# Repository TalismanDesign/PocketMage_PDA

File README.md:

# PocketMage PDA

PocketMage is available on Crowd Supply! Check it out [there](https://pocketmage.org/back)!

@Ashtf 2025

<!-- markdownlint-disable MD033 -->

## [Project Summary]

  This project is a PDA powered by an ESP32-S3 running a custom OS written in C++ using PlatformIO. This project utilizes an E-Ink and OLED screen in tandem to mitigate the refresh rate restrictions of an E-Ink panel while retaining the aesthetics and benefits of using E-Ink. This project is a work in progress and currently amounts to a simple GUI for navigating between apps, a text (.txt) file editor, and a basic file manager. More applications are planned for the future and a list of TO-DOs can be found below.

  At this point, the plan for this project is to get the software and hardware to maturity and once a finished product is achieved, a few things will happen. First, the project files (Code, KiCad schematics, 3D files) will be open-sourced and free for anyone to access. Next, I will likely begin selling kits that allow people to purchase all the parts required to build a device for themselves if they don't want to source the parts themselves. Finally, the community will be encouraged to help develop the software for the device and hopefully push it even further than I could myself.

The project is open hardware and open software: the code, KiCad schematics, and 3D files are published under Apache-2.0. Kits are available on [Crowd Supply](https://pocketmage.org/back) for anyone who prefers not to source parts individually. Community contributions to the firmware and apps are welcome.

## [Getting Started]

Start with the docs sites. The PocketMageOS docs cover the device, the OS, and the built-in apps; the SDK docs cover building standalone apps.

- [PocketMageOS Docs](https://talismandesign.github.io/PocketMage_PDA/docs/)
- [Architecture](https://talismandesign.github.io/PocketMage_PDA/docs/development/architecture)
- [Build Environments](https://talismandesign.github.io/PocketMage_PDA/docs/development/build-environments)
- [Command Manual](https://talismandesign.github.io/PocketMage_PDA/docs/command-manual)
- [FAQ](https://talismandesign.github.io/PocketMage_PDA/docs/faq)
- [Scripting](https://talismandesign.github.io/PocketMage_PDA/docs/scripting)
- [PocketMage SDK Docs](https://talismandesign.github.io/PocketMage_SDK/docs/)

Apps come in two forms. **Native apps** compile into the firmware; start from [APP_TEMPLATE.cpp](./Code/PocketMageOS/src/APP_TEMPLATE.cpp) and the [App API Reference](https://talismandesign.github.io/PocketMage_PDA/docs/reference/app-api). **ELF apps** build standalone against the SDK and load from the SD card at runtime; start from the [SDK Get Started guide](https://talismandesign.github.io/PocketMage_SDK/docs/get-started/).

The app walkthrough video is a useful first pass: [Developing For the PocketMage](https://www.youtube.com/watch?v=3Ytc-3-BbMM).

## [Hardware]

- ESP32-S3 WROOM1 with 16 MB flash and 8 MB RAM. WiFi and Bluetooth supported.
- 3.1" 320x240px 1-bit SPI E-Ink panel (GDEQ031T10) with integrated driver
- 256x32px 1-bit SPI OLED (SSD1326, ER-OLED018-1W) with integrated driver
- MicroSD card slot with support for up to 2 TB
- TCA8418 I2C keyboard matrix IC
- Piezo buzzer (simple tones)
- Power button
- 1200 mAh pouch-style LiPo battery with JST PH (2 mm) connector
- USB Type-C connector
- PCF8563T I2C RTC module
- Expansion port with the following breakouts:
  - +3.3V
  - GND
  - I2C SDA
  - I2C SCL
  - SPI MOSI
  - SPI SCK
  - SPI MISO
  - GPIO A
  - GPIO B
  - GPIO C
  - GPIO D / UART TX (changeable with a solder jumper, default TX)
  - GPIO E / UART RX (changeable with a solder jumper, default RX)

## [Software]

- Text editor app (TXT)
- FileWiz file-management app
- Calendar app
- USB file transfer app
- COMM mesh chat app
- Settings app
- Tasks app
- Journal app
- Dictionary app (Lexicon)
- App loader for ELF apps
- Terminal app (Wrench scripting)
- SSH
- Commands supported through the home menu:
  - `roll dN` (dice roll, N = number of sides)
  - set time and date
  - directly open files in TXT or FileWiz by typing the name
  - and more

## [Planned Features]

- Timers and alarms
- E-book reader
- WiFi notes/calendar sync (Google Docs/Calendar)
- LoRa/Meshtastic add-on module
- Battery expansion add-on module
- Custom abbreviations
- Bluetooth keyboard support

## License

All files are distributed under the Apache-2.0 license:

PocketMage PDA - A clamshell note-taking and productivity device using E-Ink and OLED.

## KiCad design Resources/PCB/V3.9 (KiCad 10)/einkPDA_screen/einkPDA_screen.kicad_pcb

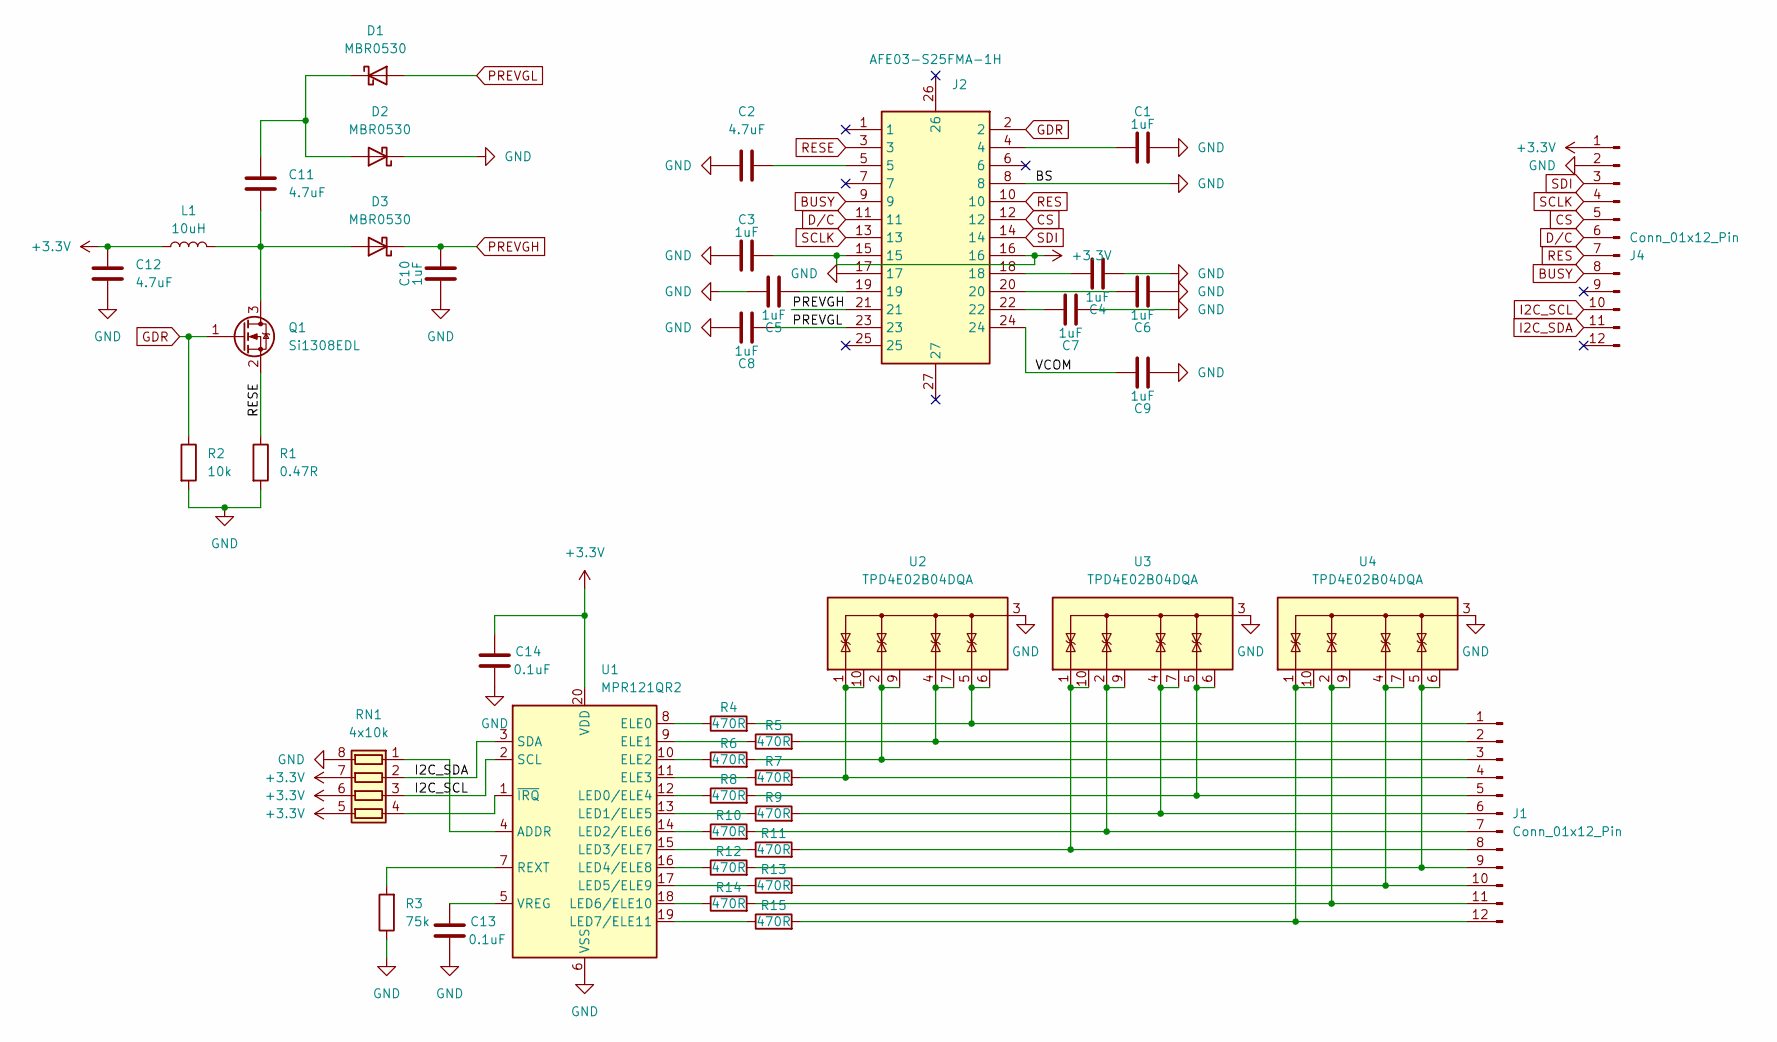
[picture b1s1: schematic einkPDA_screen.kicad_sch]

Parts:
C1, C3, C4, C5, C6, C7, C8, C9, C10: 1uF; C_0402_1005Metric; MPN C52923
C2, C11, C12: 4.7uF; C_0805_2012Metric; MPN C1779
C13, C14: 0.1uF; C_0402_1005Metric; MPN C1525
D1, D2, D3: MBR0530; D_SOD-123; MPN C77336
J1: Conn_01x12_Pin; TouchSlider-12_50x10mm
J2: AFE03-S25FMA-1H; MPN C262544
J4: Conn_01x12_Pin; AFC01-S12FCA-00; MPN C262661
L1: 10uH; L_Cenker_CKCS5020; MPN C52281
Q1: Si1308EDL; SOT-323_SC-70; MPN C7603347
R1: 0.47R; R_0603_1608Metric; MPN C3013349
R2: 10k; R_0805_2012Metric; MPN C17414
R3: 75k; R_0603_1608Metric; MPN C23242
R4, R5, R6, R7, R8, R9, R10, R11, R12, R13, R14, R15: 470R; R_0402_1005Metric; LCSC Part # C25117
RN1: 4x10k; R_Array_Concave_4x0603; MPN C29718
U1: MPR121QR2; UQFN-20_3x3mm_P0.4mm; MPN C91322
U2, U3, U4: TPD4E02B04DQA; USON-10_2.5x1.0mm_P0.5mm

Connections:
+3.3V: C3.2, C12.1, C14.1, J2.15, J2.16, J4.1, L1.1, RN1.5 (R4.2), RN1.6 (R3.2), RN1.7 (R2.2), U1.20 (VDD)
/VCOM: C9.2, J2.24
BUSY: J2.9, J4.8
CS: J2.12, J4.5
D/C: J2.11, J4.6
GDR: J2.2, Q1.1 (G), R2.1
GND: C1.2, C2.1, C3.1, C4.1, C5.2, C6.1, C7.1, C8.2, C9.1, C10.1, C12.2, C13.2, C14.2, D2.1 (K), J2.8, J2.17, J4.2, R1.2, R2.2, R3.1, RN1.8 (R1.2), U1.6 (VSS), U2.3 (G), U2.8 (G), U3.3 (G), U3.8 (G), U4.3 (G), U4.8 (G)
I2C_SCL: J4.10, RN1.3 (R3.1), U1.2 (SCL)
I2C_SDA: J4.11, RN1.2 (R2.1), U1.3 (SDA)
unnamed: C1.1, J2.4
unnamed: C2.2, J2.5
unnamed: C4.2, J2.18
unnamed: C5.1, J2.19
unnamed: C6.2, J2.20
unnamed: C7.2, J2.22
unnamed: C11.1, D1.1 (K), D2.2 (A)
unnamed: C11.2, D3.2 (A), L1.2, Q1.3 (D)
unnamed: J1.1, R4.2, U2.5 (IO4), U2.6 (NC)
unnamed: J1.2, R5.2, U2.4 (IO3), U2.7 (NC)
unnamed: J1.3, R6.2, U2.2 (IO2), U2.9 (NC)
unnamed: J1.4, R7.2, U2.1 (IO1), U2.10 (NC)
unnamed: J1.5, R8.2, U3.5 (IO4), U3.6 (NC)
unnamed: J1.6, R9.2, U3.4 (IO3), U3.7 (NC)
unnamed: J1.7, R10.2, U3.2 (IO2), U3.9 (NC)
unnamed: J1.8, R11.2, U3.1 (IO1), U3.10 (NC)
unnamed: J1.9, R12.2, U4.5 (IO4), U4.6 (NC)
unnamed: J1.10, R13.2, U4.4 (IO3), U4.7 (NC)
unnamed: J1.11, R14.2, U4.2 (IO2), U4.9 (NC)
unnamed: J1.12, R15.2, U4.1 (IO1), U4.10 (NC)
unnamed: RN1.1 (R1.1), U1.4 (ADDR)
unnamed: RN1.4 (R4.1), U1.1 (~IRQ)
unnamed: R4.1, U1.8 (ELE0)
unnamed: R5.1, U1.9 (ELE1)
unnamed: R6.1, U1.10 (ELE2)
unnamed: R7.1, U1.11 (ELE3)
unnamed: R8.1, U1.12 (LED0/ELE4)
unnamed: R9.1, U1.13 (LED1/ELE5)
unnamed: R10.1, U1.14 (LED2/ELE6)
unnamed: R11.1, U1.15 (LED3/ELE7)
unnamed: R12.1, U1.16 (LED4/ELE8)
unnamed: R13.1, U1.17 (LED5/ELE9)
unnamed: R14.1, U1.18 (LED6/ELE10)
unnamed: R15.1, U1.19 (LED7/ELE11)
unnamed: R3.2, U1.7 (REXT)
unnamed: C13.1, U1.5 (VREG)
PREVGH: C10.2, D3.1 (K), J2.21
PREVGL: C8.1, D1.2 (A), J2.23
RES: J2.10, J4.7
RESE: J2.3, Q1.2 (S), R1.1
SCLK: J2.13, J4.4
SDI: J2.14, J4.3

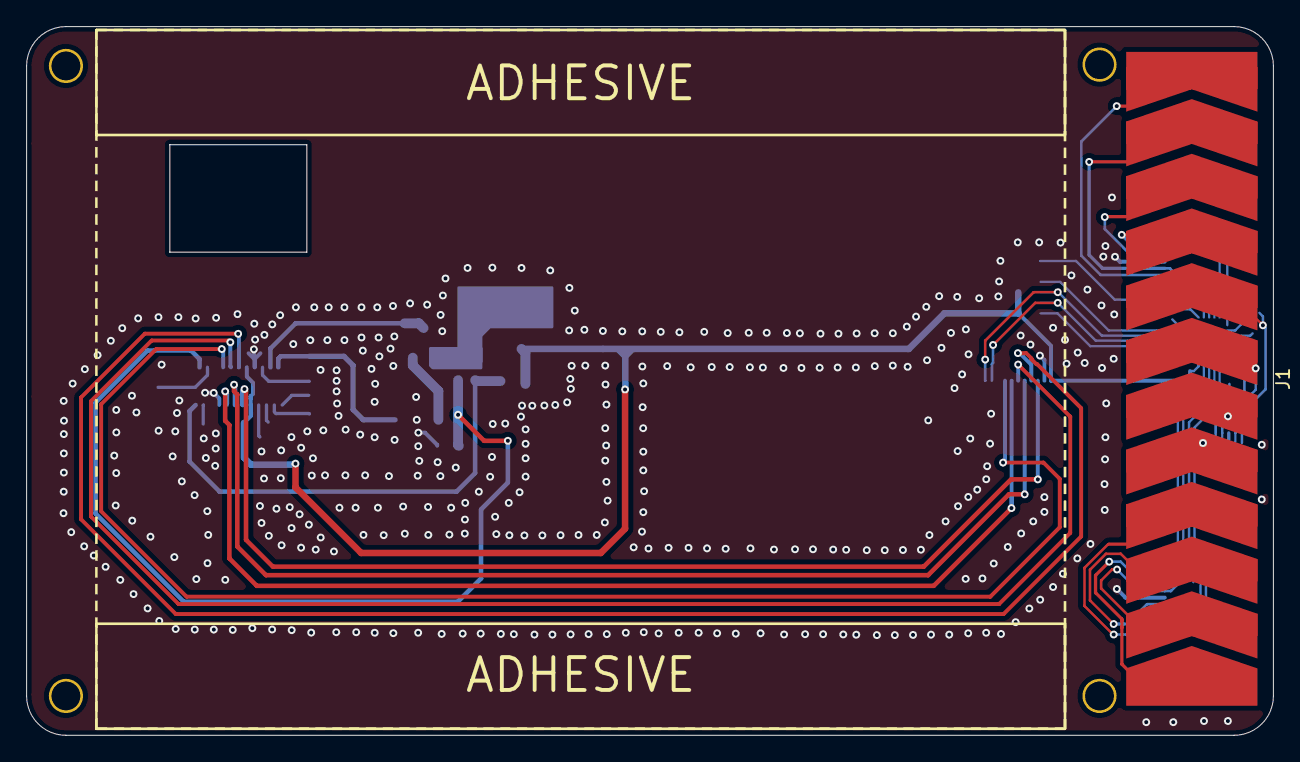
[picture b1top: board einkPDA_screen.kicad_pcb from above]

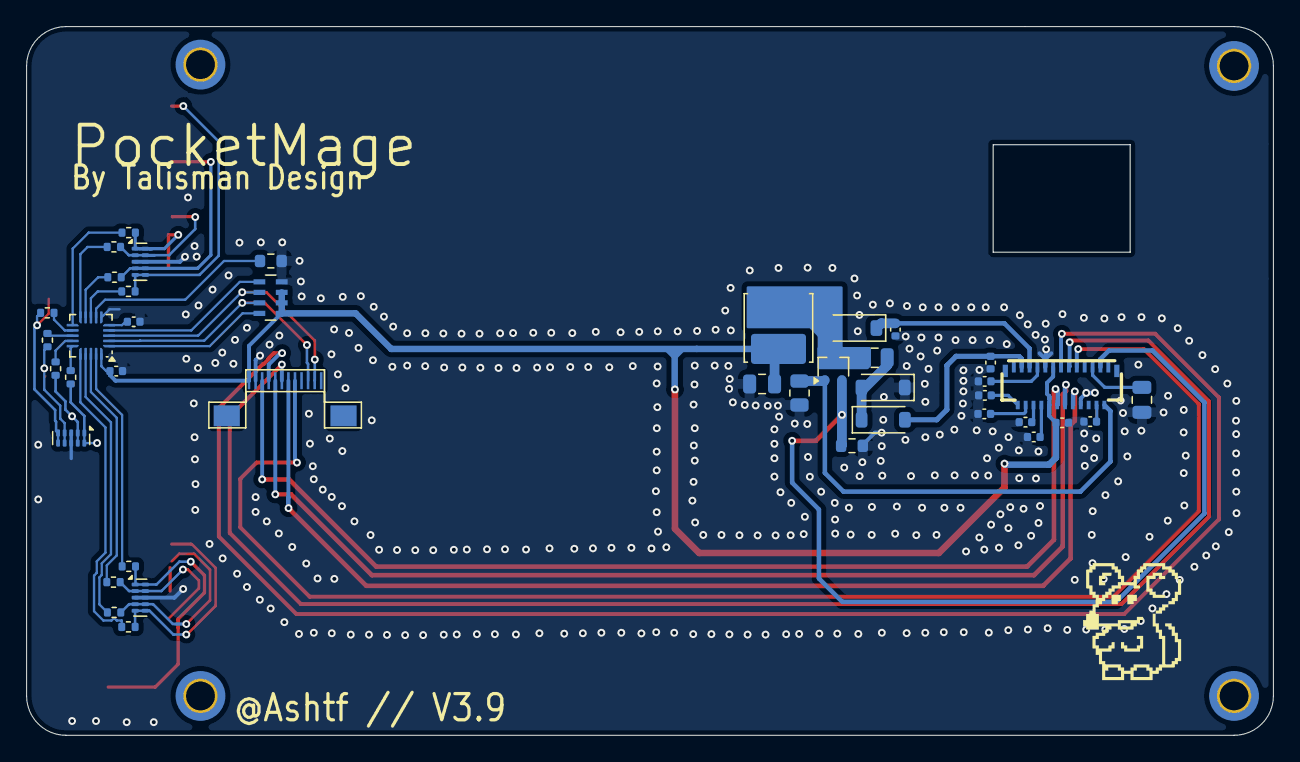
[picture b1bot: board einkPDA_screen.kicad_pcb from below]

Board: 2 copper layers, 95.0 x 54.0 mm, 42 parts (41 on the bottom side), 51 nets.

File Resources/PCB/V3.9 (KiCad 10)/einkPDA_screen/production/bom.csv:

Designator,Footprint,Quantity,Value,LCSC Part #
"C1, C10, C3, C4, C5, C6, C7, C8, C9",0402,9,1uF,C52923
"C11, C12, C2",0805,3,4.7uF,C1779
"C13, C14",0402,2,0.1uF,C1525
"D1, D2, D3",D_SOD-123,3,MBR0530,C77336
J1,TouchSlider-12_50x10mm,1,Conn_01x12_Pin,
J2,AFE03-S25FMA-1H,1,~,C262544
J4,AFC01-S12FCA-00,1,Conn_01x12_Pin,C262661
L1,L_Cenker_CKCS5020,1,10uH,C52281
Q1,SOT-323_SC-70,1,Si1308EDL,C7603347
R1,0603,1,0.47R,C3013349
"R10, R11, R12, R13, R14, R15, R4, R5, R6, R7, R8, R9",0402,12,470R,C25117
R2,0805,1,10k,C17414
R3,0603,1,75k,C23242
RN1,R_Array_Concave_4x0603,1,4x10k,C29718
U1,UQFN-20_3x3mm_P0.4mm,1,MPR121QR2,C91322
"U2, U3, U4",USON-10_2.5x1.0mm_P0.5mm,3,TPD4E02B04DQA,

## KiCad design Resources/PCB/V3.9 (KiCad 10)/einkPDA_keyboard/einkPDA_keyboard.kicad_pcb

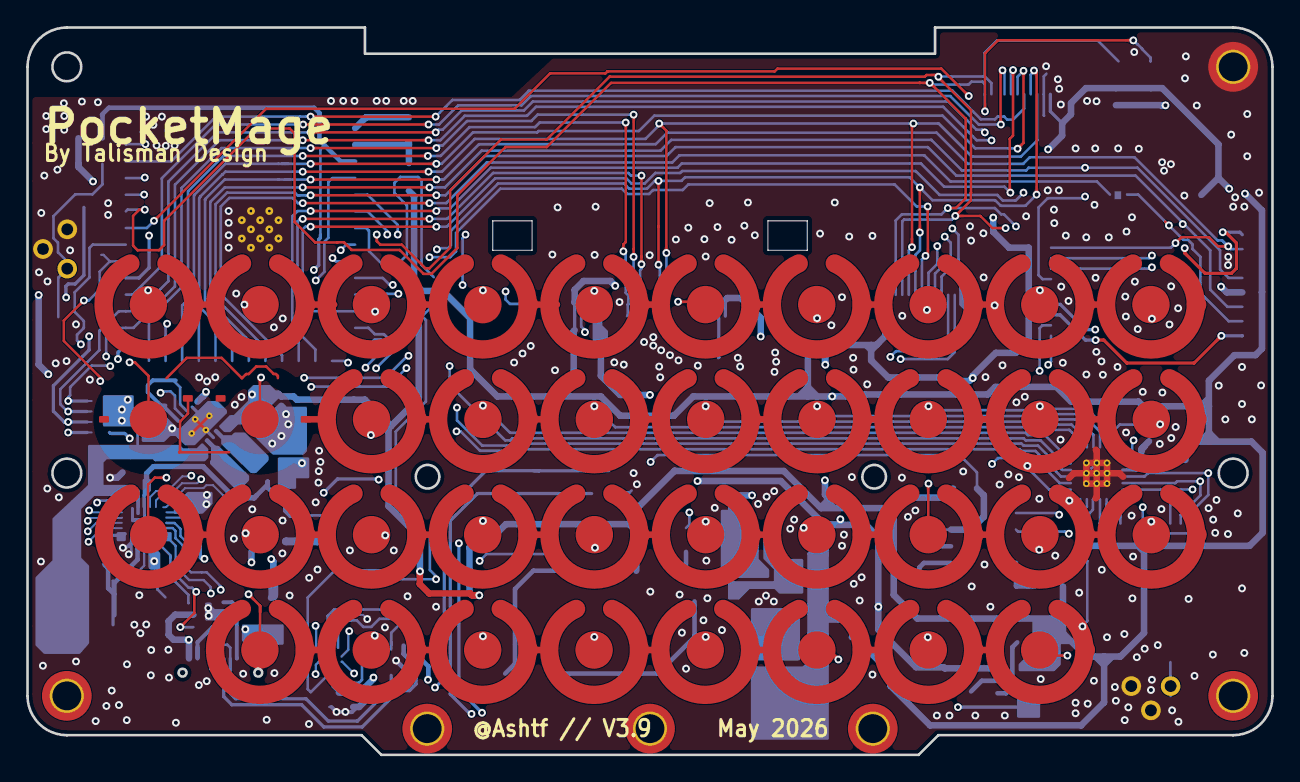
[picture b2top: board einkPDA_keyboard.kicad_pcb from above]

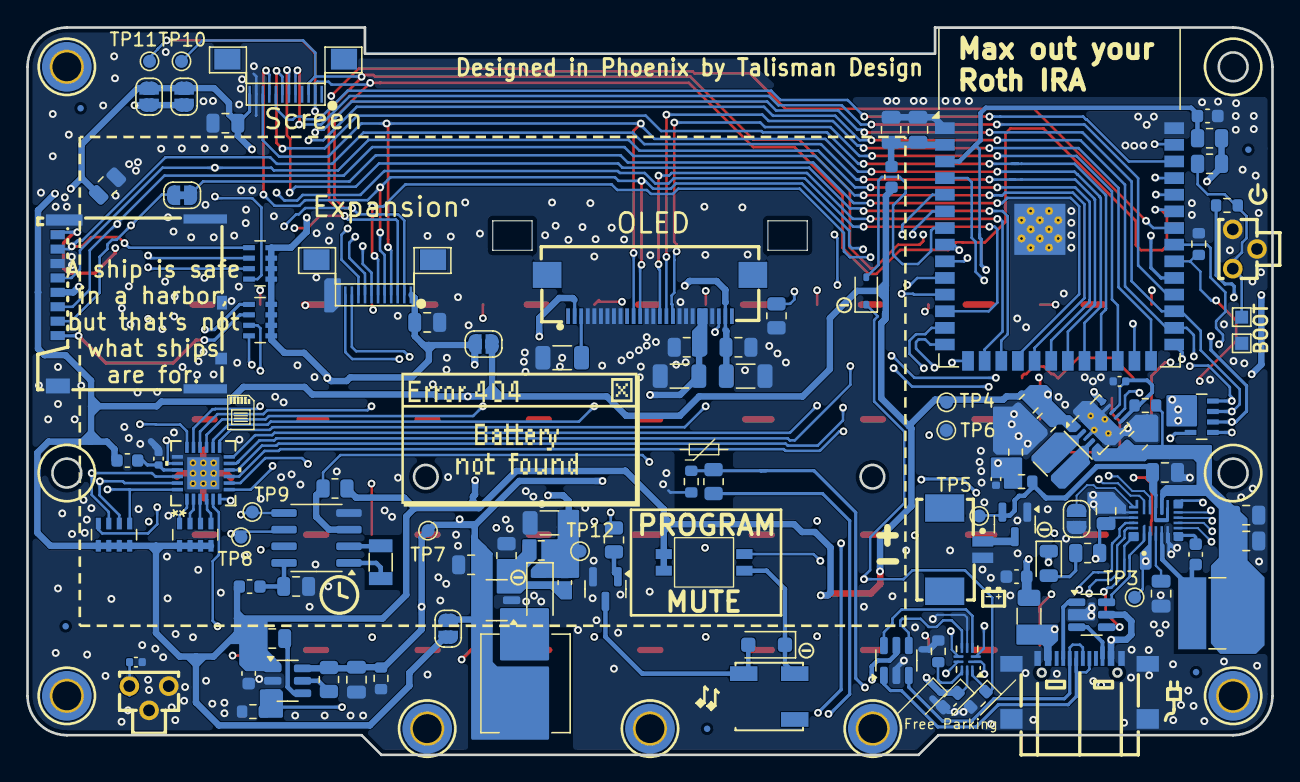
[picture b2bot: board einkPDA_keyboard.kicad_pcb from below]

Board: 4 copper layers, 95.0 x 55.5 mm, 148 parts (110 on the bottom side), 106 nets.

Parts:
BZ1: Buzzer; BUZ-SMD_3P_L5.0-W5.0-P3.50-TL
C1, C4, C6, C20: 1uF; C_0603_1608Metric
C2, C9: 100nF; C_0805_2012Metric
C3, C21, C22: 22uF; C_0805_2012Metric
C5: 47uF; C_0805_2012Metric
C7, C8, C19, C33: 0.1uF; C_0402_1005Metric
C10, C23, C24, C26, C28, C29, C30, C31, C32: 10uF; C_0805_2012Metric
C11: 4.7pF; C_0603_1608Metric
C12, C13, C14, C16: 4.7uF; C_1206_3216Metric
C15, C17: .1uF; C_0805_2012Metric
C18: 680pF; C_0805_2012Metric
C25: 4.7uF; C_0805_2012Metric
C27: 22nF; C_0603_1608Metric
D1: KT-0805Y; LED_0805_2012Metric
D2: MBR0530; D_SOD-123
D3: SM4007; D_SOD-123F
D5: D_Schottky; D_SOD-323
F1: 3A FUSE; Fuse_1206_3216Metric
FB1, FB2, FB3: FerriteBead; L_0603_1608Metric
J1: USB_C_Receptacle_USB2.0_16P; USB-TYPE-C-SMD_TYPE-C-16P-QTWT
J2, J5: Conn_01x12_Pin; AFC01-S12FCA-00
J3: Conn_01x26_Pin; FPC-SMD_AFC24-S26FIA [DUAL-SIDE]
J4: Micro_SD_Card; TF-SMD_503398-1892
J6: C2764211; CONN-SMD_532610271
JP1: SolderJumper_2_Bridged; SolderJumper-2_P1.3mm_Bridged_RoundedPad1.0x1.5mm
JP2, JP6, JP7, JP8, JP9: SolderJumper_2_Open; SolderJumper-2_P1.3mm_Open_RoundedPad1.0x1.5mm
L1: 10uH; L_Chilisin_BMRx00060630
L2: 1uH; L_Ferrocore_DLG-0504
L3: 2.2uH; L_Wurth_WE-LQSH-3012
Q1: MMBT3904; SOT-23
Q2: AO3401A; SOT-23
R1, R14: 10K; R_0805_2012Metric
R2, R8: 100R; R_0603_1608Metric
R3: 4.7k; R_0603_1608Metric
R4: 1k; R_0603_1608Metric
R5, R15: 470R; R_0805_2012Metric
R6, R7, R9, R19: 100K; R_0603_1608Metric
R11, R16: 2k; R_0805_2012Metric
R12: 1.8M; R_0805_2012Metric
R13: 205k; R_0805_2012Metric
R17: 10k; R_0805_2012Metric
R18: 10k; R_0603_1608Metric
R20: 680k; R_0805_2012Metric
RN1, RN2, RN3, RN4, RN5: 4x10k; R_Array_Concave_4x0603
SW1, SW3, SW5, SW6, SW7, SW9, SW10, SW11, SW12, SW13, SW14, SW15, SW16, SW17, SW18, SW19, SW20, SW21, SW22, SW23, SW24, SW25, SW26, SW27, SW28, SW29, SW30, SW31, SW32, SW33, SW34, SW35, SW37, SW38, SW39, SW40: contact_pad_SINGLE
SW2: contactPad_cutoutR
SW4: SW_DIP_x02; 2X_DIP_DHN-02-V-TR
SW8: contactPad_cutoutL
SW36, SW41: YTS-C017-2B; KEY-TH_3P-L4.5-W4.5-P3.0-EH
TH1: NTC; R_0603_1608Metric
TP1, TP2: TestPoint; TestPoint_Pad_1.0x1.0mm
TP3, TP4, TP5, TP6, TP7, TP8, TP9, TP10, TP11, TP12: TestPoint; TestPoint_Pad_D1.0mm
U1: ESP32-S3-WROOM-1-N16R2; ESP32-S3-WROOM-1
U2, U6: USBLC6-2SC6; SOT-23-6
U3: TPS63001; Texas_DRC0010J_ThermalVias
U4: PCF8563T; SOIC-8_3.9x4.9mm_P1.27mm
U5: TCA8418RTWR; RTW24_2P45X2P45
U7: TPS61040DBV; SOT-23-5
U8: TPS22917DBV; SOT-23-6
U9: MP2722GRH-0000-Z; IC_MP2722GRH-0000-Z
U10: TS3USB30ERSWR; UQFN-10_1.4x1.8mm_P0.4mm
Y1: Crystal_32.768kHz; Crystal_SMD_3215-2Pin_3.2x1.5mm

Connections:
+3.3V: C4.2, C6.2, C18.1, C31.2, C32.2, FB1.1, FB2.2, FB3.1, JP2.2 (B), JP7.2 (B), JP8.2 (B), JP9.2 (B), R1.1, R11.2, R14.1, RN1.1 (R1.1), RN1.2 (R2.1), RN1.3 (R3.1), RN1.4 (R4.1), RN2.5 (R4.2), RN2.6 (R3.2), RN2.7 (R2.2), RN2.8 (R1.2), RN4.5 (R4.2), RN4.6 (R3.2), RN4.7 (R2.2), SW4.1, SW4.2, TP4.1 (1_1), U3.1 (VOUT), U3.10 (FB), U8.1 (VIN), U10.9 (VCC)
+12V: C11.2, C12.1, C13.1, C15.1, D2.1 (K), J3.2, J3.25, R12.1, TP12.1 (1_1)
BAT+: C26.2, Q2.2 (S), R6.1, TP5.1 (1_1), U9.12 (BATTSNS), U9.14 (BATT)
BAT_MEAS: C19.1, R6.2, R7.1, U1.4 (IO4)
BMS_INT: RN4.4 (R4.1), U1.33 (IO40), U9.8 (~INT)
BOOT: R8.1, R14.2, SW36.1, TP1.1 (1_1)
BUZZER: R15.1, U1.10 (IO17)
BZ_CUTOFF: BZ1.1 (+), D3.1 (K), SW4.3
E-PAPER_BUSY: J2.5, U1.30 (IO37)
E-PAPER_CS: J2.8, U1.38 (IO2)
E-PAPER_D/C: J2.7, U1.23 (IO21)
E-PAPER_RES: J2.6, U1.17 (IO9)
EN: C1.2, C33.1, R1.2, SW41.1, U1.3 (EN)
ESP_D+: U1.14 (IO20), U10.2 (D2+)
ESP_D-: U1.13 (IO19), U10.6 (D2-)
EX_A: J5.7, U1.15 (IO3)
EX_B: J5.8, U1.11 (IO18)
EX_C: J5.9, U1.34 (IO41)
GND: C1.1, C2.1, C3.1, C4.1, C5.2, C6.1, C7.2, C8.2, C9.1, C10.1, C12.2, C13.2, C14.2, C15.2, C16.2, C17.2, C19.2, C20.1, C21.1, C22.1, C23.1, C24.2, C25.2, C26.1, C28.1, C29.1, C30.1, C31.1, C32.1, C33.2, J1.A1 (GND), J1.A12 (GND), J1.S1 (SHIELD), J2.11, J3.4, J3.5, J3.6, J3.7, J3.8, J3.9, J3.13, J3.14, J3.18, J3.19, J3.20, J3.23, J4.6 (VSS), J4.9 (SHIELD), J5.12, J6.3 (BATT-), JP6.1 (A), Q1.2 (E), Q2.1 (G), R3.2, R4.2, R7.2, R9.2, R13.2, R18.2, R19.2, R20.2, SW36.2, SW36.3 (GND), SW41.2, SW41.3 (GND), TH1.2, TP2.1 (1_1), TP6.1 (1_1), U1.1 (GND), U1.40 (GND), U1.41 (GND), U2.2 (GND), U3.3 (PGND), U3.9 (GND), U3.11 (PGND), U4.4 (VSS), U5.19 (GND), U5.25 (EPAD), U6.2 (GND), U7.2 (GND), U8.2 (GND), U9.5 (PGND), U9.18 (AGND), U10.4 (GND)
I2C_SCL: RN1.6 (R3.2), RN4.2 (R2.1), TP8.1 (1_1), U1.28 (IO35), U4.6 (SCL), U5.23 (SCL), U9.16 (SCL)
I2C_SCL_SWITCHED: J2.3, J5.3, RN5.7 (R2.2), TP10.1 (1_1), U1.25 (IO48)
I2C_SDA: RN1.7 (R2.2), RN4.3 (R3.1), TP9.1 (1_1), U1.29 (IO36), U4.5 (SDA), U5.22 (SDA), U9.15 (SDA)
I2C_SDA_SWITCHED: J2.2, J5.2, RN5.8 (R1.2), TP11.1 (1_1), U1.35 (IO42)
IC_D+: U9.21 (D+), U10.1 (D1+)
IC_D-: U9.20 (D-), U10.7 (D1-)
KB_INT: RN1.5 (R4.2), U1.12 (IO8), U5.24 (*INT)
LOAD: R19.1, U1.31 (IO38), U8.3 (ON)
unnamed: BZ1.2 (-), D3.2 (A), Q1.3 (C)
unnamed: D1.2 (A), R16.1
unnamed: D1.1 (K), U9.11 (STAT/IB)
unnamed: D2.2 (A), L1.2, U7.1 (SW)
unnamed: D5.1 (K), R18.1, SW4.4, U10.10 (S)
unnamed: J1.A5 (CC1), U6.1 (I/O1)
unnamed: J1.B5 (CC2), U6.3 (I/O2)
unnamed: J1.A6 (D+), J1.B6 (D+), U2.1 (I/O1)
unnamed: J1.A7 (D-), J1.B7 (D-), U2.3 (I/O2)
unnamed: C14.1, J3.3
unnamed: J3.24, R20.1
unnamed: J4.2 (DAT3/CD), JP1.2 (B), RN3.7 (R2.2)
unnamed: J6.1 (BATT+), Q2.3 (D)
unnamed: JP6.2 (B), U9.17 (~RST)
unnamed: Q1.1 (B), R15.2
unnamed: RN1.8 (R1.2), U5.20 (*RESET)
unnamed: RN2.1 (R1.1), U5.4 (ROW4)
unnamed: RN2.2 (R2.1), U5.3 (ROW5)
unnamed: RN2.3 (R3.1), U5.2 (ROW6)
unnamed: RN2.4 (R4.1), U5.1 (ROW7)
unnamed: RN4.1 (R1.1), U9.9 (PG/NTC2)
unnamed: C25.1, R16.2, RN4.8 (R1.2), U9.19 (VCC)
unnamed: C2.2, C3.2, FB1.2, U1.2 (3V3)
unnamed: R8.2, U1.27 (IO0)
unnamed: F1.1, J1.A4 (VBUS), J1.A9 (VBUS), U2.5 (VBUS), U6.5 (VBUS)
unnamed: C7.1, R2.1, U3.6 (EN), U3.8 (VINA)
unnamed: L3.1, U3.4 (L1)
unnamed: L3.2, U3.2 (L2)
unnamed: U4.1 (OSCI), Y1.1
unnamed: U4.2 (OSCO), Y1.2
unnamed: C9.2, FB3.2, U4.8 (VDD)
unnamed: C8.1, FB2.1, U5.21 (VCC)
unnamed: C11.1, R12.2, R13.1, U7.3 (FB)
unnamed: C18.2, U8.4 (CT)
unnamed: R5.2, U8.5 (QOD)
unnamed: C27.2, U9.6 (BST)
unnamed: U6.6 (I/O1), U9.1 (CC1)
unnamed: U6.4 (I/O2), U9.22 (CC2)
unnamed: R17.1, TH1.1, U9.10 (NTC1)
unnamed: C23.2, U9.3 (PMID)
unnamed: C27.1, L2.1, U9.4 (SW)
unnamed: R17.2, U9.7 (VRNTC)
unnamed: R3.1, U10.8 (~OE)
OLED_CS: J3.17, U1.24 (IO47)
OLED_D/C: J3.15, U1.16 (IO46)
OLED_RES: J3.16, U1.26 (IO45)
PWR_SAVE: R9.1, U1.32 (IO39), U3.7 (PS/SYNC)
RTC_INT: R11.1, U1.39 (IO1), U4.3 (~INT)
RX: J5.11, U1.36 (RXD0)
SD_CLK: J4.5 (CLK), RN3.8 (R1.2), U1.20 (IO12)
SD_CMD: J4.3 (CMD), RN3.6 (R3.2), U1.19 (IO11)
SD_CS: JP1.1 (A), U1.18 (IO10)
SD_D0: J4.7 (DAT0), RN3.5 (R4.2), U1.21 (IO13)
SD_D1: J4.8 (DAT1), RN5.5 (R4.2), U1.5 (IO5)
SD_D2: J4.1 (DAT2), RN5.6 (R3.2), U1.6 (IO6)
SPI_MISO_SWITCHED: J5.6, U1.9 (IO16)
SPI_MOSI_SWITCHED: J2.10, J3.11, J5.4, U1.22 (IO14)
SPI_SCK_SWITCHED: J2.9, J3.12, J5.5, U1.8 (IO15)
TX: J5.10, U1.37 (TXD0)
USB_5V: C20.2, F1.2, TP3.1 (1_1), U9.2 (IN)
USB_D+: U2.6 (I/O1), U10.3 (D+)
USB_D-: U2.4 (I/O2), U10.5 (D-)
USB_SW: D5.2 (A), U1.7 (IO7)
V_LOADSWITCH: C5.1, C10.2, C16.1, C17.1, C21.2, C22.2, C24.1, J2.12, J3.21, J3.22, J4.4 (VDD), J5.1, JP2.1 (A), JP7.1 (A), JP8.1 (A), JP9.1 (A), L1.1, R4.1, R5.1, RN3.1 (R1.1), RN3.2 (R2.1), RN3.3 (R3.1), RN3.4 (R4.1), RN5.1 (R1.1), RN5.2 (R2.1), RN5.3 (R3.1), RN5.4 (R4.1), TP7.1 (1_1), U7.4 (EN), U7.5 (VIN), U8.6 (VOUT)
V_SYS: C28.2, C29.2, C30.2, L2.2, R2.2, U3.5 (VIN), U9.13 (SYS)
col1: SW1.1, SW2.1, SW3.1, U5.9 (COL0)
col2: SW7.1, SW8.1, SW9.1, SW10.1, U5.10 (COL1)
col3: SW13.1, SW14.1, SW15.1, SW16.1, U5.11 (COL2)
col4: SW19.1, SW20.1, SW21.1, SW22.1, U5.12 (COL3)
col5: SW25.1, SW26.1, SW27.1, SW28.1, U5.13 (COL4)
col6: SW31.1, SW32.1, SW33.1, SW34.1, U5.14 (COL5)
col7: SW37.1, SW38.1, SW39.1, SW40.1, U5.15 (COL6)
col8: SW5.1, SW6.1, SW11.1, SW12.1, U5.16 (COL7)
col9: SW17.1, SW18.1, SW23.1, SW24.1, U5.17 (COL8)
col10: SW29.1, SW30.1, SW35.1, U5.18 (COL9)
row1: SW1.2, SW5.2, SW7.2, SW13.2, SW17.2, SW19.2, SW25.2, SW29.2, SW31.2, SW37.2, U5.8 (ROW0)
row2: SW2.2, SW6.2, SW8.2, SW14.2, SW18.2, SW20.2, SW26.2, SW30.2, SW32.2, SW38.2, U5.7 (ROW1)
row3: SW3.2, SW9.2, SW11.2, SW15.2, SW21.2, SW23.2, SW27.2, SW33.2, SW35.2, SW39.2, U5.6 (ROW2)
row4: SW10.2, SW12.2, SW16.2, SW22.2, SW24.2, SW28.2, SW34.2, SW40.2, U5.5 (ROW3)

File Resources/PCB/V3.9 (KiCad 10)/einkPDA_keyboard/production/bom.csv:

Designator,Footprint,Quantity,Value,LCSC Part #
BZ1,BUZ-SMD_3P_L5.0-W5.0-P3.50-TL,1,Buzzer,C781883
"C1, C20, C4, C6",0603,4,1uF,C15849
"C10, C23, C24, C26, C28, C29, C30, C31, C32",0805,9,10uF,C15850
C11,0603,1,4.7pF,C1669
"C12, C13, C14, C16",1206,4,4.7uF,C29823
"C15, C17",0805,2,.1uF,C28233
C18,0805,1,680pF,C1754
"C19, C33, C7, C8",0402,4,0.1uF,C1525
"C2, C9",0805,2,100nF,C49678
"C21, C22, C3",0805,3,22uF,C45783
C25,0805,1,4.7uF,C1779
C27,0603,1,22nF,C21122
C5,0805,1,47uF,C124129
D1,0805,1,KT-0805Y,C2296
D2,D_SOD-123,1,MBR0530,C77336
D3,D_SOD-123F,1,SM4007,C64898
D5,D_SOD-323,1,D_Schottky,C191023
F1,1206,1,3A FUSE,C2843999
"FB1, FB2, FB3",0603,3,FerriteBead,C85831
J1,USB-TYPE-C-SMD_TYPE-C-16P-QTWT,1,USB_C_Receptacle_USB2.0_16P,C5187472
"J2, J5",AFC01-S12FCA-00,2,Conn_01x12_Pin,C262661
J3,FPC-SMD_AFC24-S26FIA [DUAL-SIDE],1,Conn_01x26_Pin,C262684
J4,TF-SMD_503398-1892,1,Micro_SD_Card,C428492
J6,CONN-SMD_532610271,1,C2764211,C2764211
L1,L_Chilisin_BMRx00060630,1,10uH,C5189958
L2,L_Ferrocore_DLG-0504,1,1uH,C2929426
L3,L_Wurth_WE-LQSH-3012,1,2.2uH,C167747 
Q1,SOT-23,1,MMBT3904,C20526
Q2,SOT-23,1,AO3401A,C15127
"R1, R14, R17",0805,3,10K,C17414
"R11, R16",0805,2,2k,C17604
R12,0805,1,1.8M,C17399
R13,0805,1,205k,C218417
"R15, R5",0805,2,470R,C17710
R18,0603,1,10k,C25804
"R19, R6, R7, R9",0603,4,100K,C25803
"R2, R8",0603,2,100R,C22775
R20,0805,1,680k,C17797
R3,0603,1,4.7k,C23162
R4,0603,1,1k,C21190
"RN1, RN2, RN3, RN4, RN5",R_Array_Concave_4x0603,5,4x10k,C29718
"SW1, SW10, SW11, SW12, SW13, SW14, SW15, SW16, SW17, SW18, SW19, SW20, SW21, SW22, SW23, SW24, SW25, SW26, SW27, SW28, SW29, SW3, SW30, SW31, SW32, SW33, SW34, SW35, SW37, SW38, SW39, SW40, SW5, SW6, SW7, SW9",contact_pad_SINGLE,36,~,
"SW36, SW41",KEY-TH_3P-L4.5-W4.5-P3.0-EH,2,YTS-C017-2B,C2910872
SW4,2X_DIP_DHN-02-V-TR,1,SW_DIP_x02,C224995
TH1,0603,1,NTC,C76589
U1,ESP32-S3-WROOM-1,1,ESP32-S3-WROOM-1-N16R2,C2913205
U10,UQFN-10_1.4x1.8mm_P0.4mm,1,TS3USB30ERSWR,C73880
"U2, U6",SOT-23-6,2,USBLC6-2SC6,C7519
U3,Texas_DRC0010J_ThermalVias,1,TPS63001,C28060
U4,SOIC-8_3.9x4.9mm_P1.27mm,1,PCF8563T,C7440
U5,RTW24_2P45X2P45,1,TCA8418RTWR,C138713
U7,SOT-23-5,1,TPS61040DBV,C7722
U8,SOT-23-6,1,TPS22917DBV,C2680344
U9,IC_MP2722GRH-0000-Z,1,MP2722GRH-0000-Z,C20099551
Y1,Crystal_SMD_3215-2Pin_3.2x1.5mm,1,Crystal_32.768kHz,C5213671
